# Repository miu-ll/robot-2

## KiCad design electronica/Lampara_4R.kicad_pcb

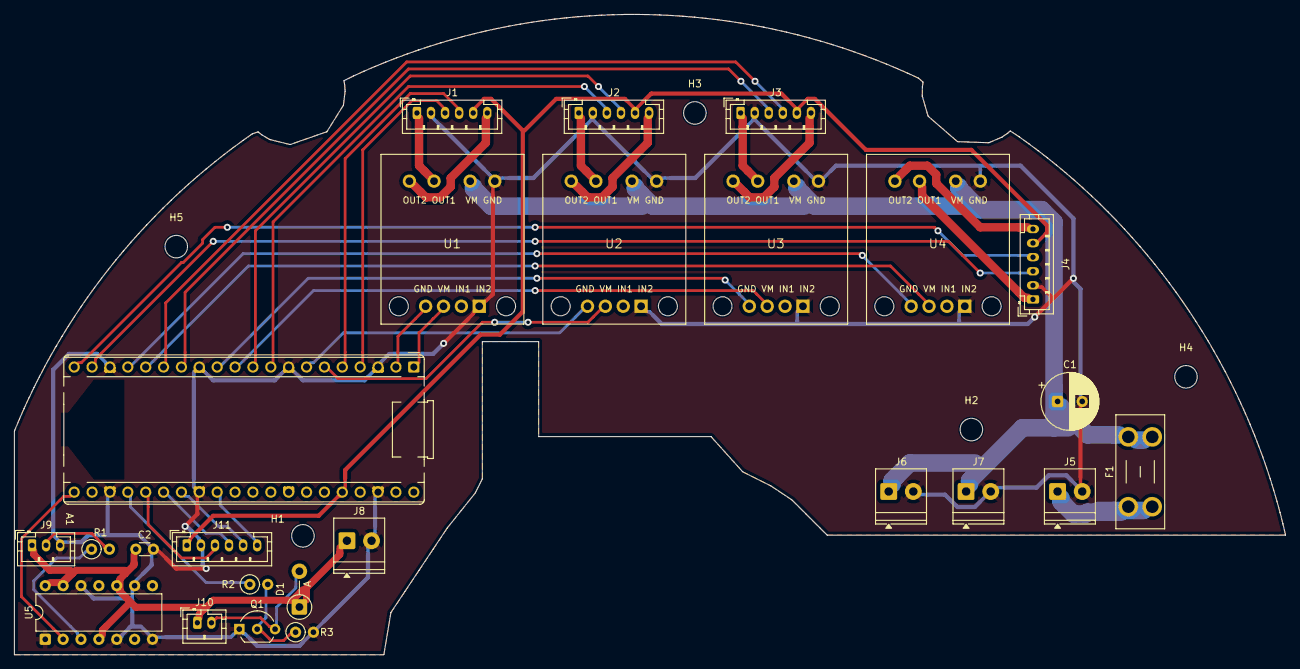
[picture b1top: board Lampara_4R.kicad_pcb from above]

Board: 2 copper layers, 180.7 x 91.0 mm, 30 parts (0 on the bottom side), 39 nets.

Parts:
A1: Raspberry Pi Pico; RaspberryPi_Pico_Common_THT
C1: 470 uF 16 V; CP_Radial_D8.0mm_P3.50mm
C2: 100 nF; C_Disc_D3.0mm_W1.6mm_P2.50mm
D1: 1N5819; D_DO-41_SOD81_P5.08mm_Vertical_AnodeUp
F1: 10 A (ATM); Fuseholder_Blade_Mini_Keystone_3568
H1, H2, H3, H4, H5: M3; MountingHole_3.2mm_M3
J1: Motor q1 (PH2.0); JST_PH_B6B-PH-K_1x06_P2.00mm_Vertical
J2: Motor q2 (PH2.0); JST_PH_B6B-PH-K_1x06_P2.00mm_Vertical
J3: Motor q3 (PH2.0); JST_PH_B6B-PH-K_1x06_P2.00mm_Vertical
J4: Motor q4 (PH2.0); JST_PH_B6B-PH-K_1x06_P2.00mm_Vertical
J5: 12 V entrada; TerminalBlock_Phoenix_PT-1,5-2-3.5-H_1x02_P3.50mm_Horizontal
J6: 12 V a XL4016; TerminalBlock_Phoenix_PT-1,5-2-3.5-H_1x02_P3.50mm_Horizontal
J7: 12 V a LM2596; TerminalBlock_Phoenix_PT-1,5-2-3.5-H_1x02_P3.50mm_Horizontal
J8: 5 V desde LM2596; TerminalBlock_Phoenix_PT-1,5-2-3.5-H_1x02_P3.50mm_Horizontal
J9: Anillo LED (PH2.0); JST_PH_B3B-PH-K_1x03_P2.00mm_Vertical
J10: Ventilador (PH2.0); JST_PH_B2B-PH-K_1x02_P2.00mm_Vertical
J11: Sensores Hall (PH2.0); JST_PH_B6B-PH-K_1x06_P2.00mm_Vertical
Q1: 2N7000; TO-92_Inline_Wide
R1: 330; R_Axial_DIN0207_L6.3mm_D2.5mm_P2.54mm_Vertical
R2: 100; R_Axial_DIN0207_L6.3mm_D2.5mm_P2.54mm_Vertical
R3: 10 k; R_Axial_DIN0207_L6.3mm_D2.5mm_P2.54mm_Vertical
U1, U2, U3, U4: Adafruit DRV8871; Adafruit_DRV8871_Portadora
U5: 74AHCT125; DIP-14_W7.62mm

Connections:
+3V3: A1.36, J1.5, J2.5, J3.5, J4.5, J11.1
+5V: C2.1, D1.1, J8.1, J9.1, J10.1, U5.4, U5.10, U5.13, U5.14
+12V: C1.1, F1.2, J6.1, J7.1, U1.7, U2.7, U3.7, U4.7
/+12V_IN: F1.1, J5.1
/ENC1_A: A1.4, J1.3
/ENC1_B: A1.5, J1.4
/ENC2_A: A1.9, J2.3
/ENC2_B: A1.10, J2.4
/ENC3_A: A1.14, J3.3
/ENC3_B: A1.15, J3.4
/ENC4_A: A1.19, J4.3
/ENC4_B: A1.20, J4.4
/HALL1: A1.25, J11.3
/HALL2: A1.26, J11.4
/HALL3: A1.27, J11.5
/HALL4: A1.29, J11.6
/LED_3V3: A1.21, U5.2
/LED_5V: R1.1, U5.3
/LED_DIN: J9.2, R1.2
/M1_N: J1.6, U1.5
/M1_P: J1.1, U1.6
/M2_N: J2.6, U2.5
/M2_P: J2.1, U2.6
/M3_N: J3.6, U3.5
/M3_P: J3.1, U3.6
/M4_N: J4.6, U4.5
/M4_P: J4.1, U4.6
/PWM1_IN1: A1.1, U1.3
/PWM1_IN2: A1.2, U1.4
/PWM2_IN1: A1.6, U2.3
/PWM2_IN2: A1.7, U2.4
/PWM3_IN1: A1.11, U3.3
/PWM3_IN2: A1.12, U3.4
/PWM4_IN1: A1.16, U4.3
/PWM4_IN2: A1.17, U4.4
/VENT_G: Q1.2, R2.2, R3.1
/VENT_N: D1.2, J10.2, Q1.3
/VENT_PWM: A1.24, R2.1
GND: A1.3, A1.8, A1.13, A1.18, A1.23, A1.28, A1.38, C1.2, C2.2, J1.2, J2.2, J3.2, J4.2, J5.2, J6.2, J7.2, J8.2, J9.3, J11.2, Q1.1, R3.2, U1.1, U1.8, U2.1, U2.8, U3.1, U3.8, U4.1, U4.8, U5.1, U5.5, U5.7, U5.9, U5.12
